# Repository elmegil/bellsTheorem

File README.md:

# bellsTheorem
[]

Bell's theorem is a proof that quantum physics is incompatible with local hidden variable theories.  The summary on Wikipedia is quite good if you’re interested in the quantum physics aspects of the theorem.

The proof is sometimes demonstrated by the use of multiple polarized lenses, as in this video:

https://www.youtube.com/watch?v=zcqZHYo7ONs&t=337s

What’s interesting is that with 3 or more polarized lenses, the behavior does not match what you might expect, namely that lens 1 reduces the light by a certain percentage, lens 2 reduces it further, and lens 3 reduces it even further, in a linear fashion.  If lens 3 and lens 1 are 90 degrees from each other, with nothing else involved, essentially no light gets through.  But if you insert lens 2 at a 45 degree angle to both of the others, suddenly there IS light getting through.  You’d expect that if 3 after 1 always blocks all the light, that would be true no matter what you put between the two.

A highly simplified explanation of this has to do with the fact that light is made up of photons, which are quantum objects.  Quantum objects behave probabilistically but ultimately are either there or not.  Photons going from lens 1 to lens 3 aren’t reduced in energy, they simply don’t pass both lenses.  However, going from one lens to one at 45 degrees only reduces the probability of photos passing by 50%.  In the process of going through, those photons then match the orientation of the second lens.  So when they get to a third lens, there is only a 45 degree angle difference there as well, and so 50% of the original 50%, or 25% of the original light, still passes through.

The rules for photons passing through polarized lenses basically are a probability that is determined entirely by the two lenses directly adjacent to the path of travel.  Any previous or subsequent lenses  aren’t considered except as a chained operation.  So with lens 1 at 0 degrees, lens 2 at 45, and lens 3 at 90 degrees (or 45 degrees from lens 2), the overall probability of a photon going from the start to the finish is 50% x 50%, or 25%.

Making things slightly weirder, the probabilities aren’t linear.  They follow a cosine squared relationship.  A photon passing through a pair of lenses at 22.5 degrees from each other is considerably more likely to pass through than the linear expectation of 75%.  In fact it’s about 85%.

============================================================================

Nyles Miszczyk on Facebook asked whether there were any modules that could process control voltages in this way.  There do not appear to be, but the idea was intriguing enough to give it a shot.  And that’s where this module comes from.

# Operational Notes

There is a single input voltage to be processed, which is normalled to +12V.  There are 4 encoders which represent the relative positions of four lenses, first to a “main” lens behind them all, and then relative to each other.  They’re arranged in a square pattern, and the input “light” (really the voltage) is processed as it goes through a single lens at 0 degrees, and then each subsequent lens.  Each of the combinations of lenses has a related output, so each of A, B, C, and D have an output that is only related to their individual angles relative to 0.  Each of AB, BC, CD, and DA has an output related to each of the intervening angles, as in the example described above; so for AB the voltage is reduced by whatever the probability is between 0 degrees and angle A, and then further reduced by whatever the probability is between the angles of A and B.  ABC, BCD, CDA, and DAB then follow the same rules for three lenses, and finally ABCD extends the process through all 4 lenses.

In addition to the encoders, each of the 4 lenses has a CV that is also related to its angle, added to the angle as set up by the encoder.  The 0 - 10V range maps to 180 degrees of rotation (positive only… need to consider doing otherwise).

On first power up, the lenses are reset to 0 degrees (but they should retain the last known state).  You can press each encoder to reset it to zero so that it’s at a known state.  If you do this by accident, pressing the encoder again takes you back to the saved state.  HOWEVER, if you zero out this way and then change things, you do do NOT save the new angle when you press again -- you just go back to the saved state, and pressing one more time takes you back to zero.

Voltage ranges: the current implementation limits inputs to 0-10V and each output will only generate 0-10V.  (and even that not very precisely).  A future revision may allow processing of bipolar input voltages, although this very likely will reduce the overall resolution.  Each input should be able to tolerate any normal Eurorack voltages outside this range (-12V to +12V), but they will be clamped at 0-10V.

Encoders:  the encoders’ positions are NOT directly mapped to the angle.  Most encoders only have about 24 steps (some have more, but none have 360 steps).  That did not seem to be a good resolution because each step would be 15 degrees.  I have mapped the encoders so that each step is 2 degrees of angle; this is why the press to reset is important so you can get back to a known angle. -- need to decide about CVs… 0 - 10V … is that 0 - 90 degrees?  0 - 180?  0 - 360?  Maybe consider 30 step encoders that do map the angle?  Is there any way to set up to display the angle, circle of LEDs on each encoder?  Is there sufficient space/bandwidth to update them?

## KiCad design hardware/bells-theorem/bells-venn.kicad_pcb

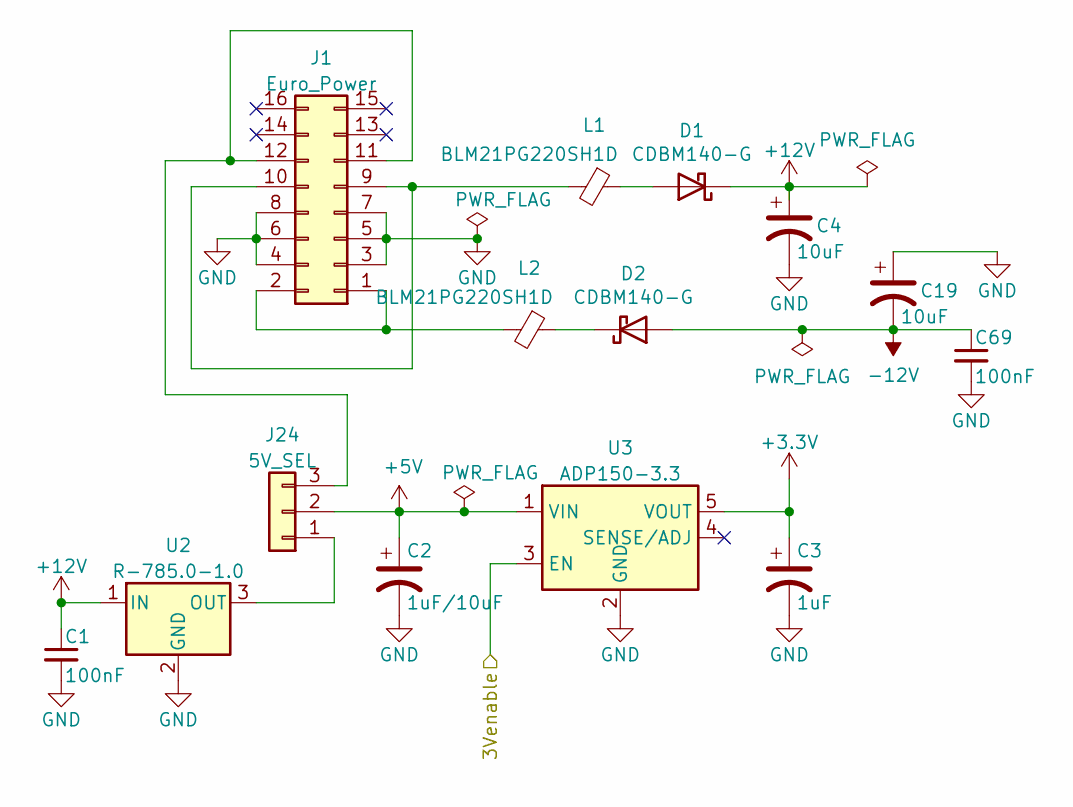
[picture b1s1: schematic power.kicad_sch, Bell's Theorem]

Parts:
C1, C69: 100nF; C_0805_2012Metric_Pad1.18x1.45mm_HandSolder
C2: 1uF/10uF; CP_Radial_D5.0mm_P2.50mm
C3: 1uF; CP_Radial_D5.0mm_P2.50mm
C4, C19: 10uF; CP_Radial_D5.0mm_P2.50mm
D1, D2: CDBM140-G; D_SMA-SMB_Universal_Handsoldering
J1: Euro_Power; IDC-Header_2x08_P2.54mm_Vertical
J24: 5V_SEL; PinHeader_1x03_P2.54mm_Vertical
L1, L2: BLM21PG220SH1D; L_0805_2012Metric_Pad1.15x1.40mm_HandSolder
U2: R-785.0-1.0; Converter_DCDC_RECOM_R-78E-0.5_THT
U3: ADP150-3.3; TSOT-23-5

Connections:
+3V3: C3.1, U3.5 (VOUT); also elsewhere on the board
+5V: C2.1, J24.2, U3.1 (VIN); also elsewhere on the board
+12V: C1.1, C4.1, D1.1 (K), U2.1 (IN); also elsewhere on the board
-12V: C19.2, C69.1, D2.2 (A); also elsewhere on the board
/main/3Venable: U3.3 (EN); also elsewhere on the board
GND: C1.2, C2.2, C3.2, C4.2, C19.1, C69.2, J1.3, J1.4, J1.5, J1.6, J1.7, J1.8, U2.2 (GND), U3.2 (GND); also elsewhere on the board
unnamed: D1.2 (A), L1.1
unnamed: D2.1 (K), L2.1
unnamed: J1.1, J1.2, L2.2
unnamed: J1.9, J1.10, L1.2
unnamed: J1.11, J1.12, J24.3
unnamed: J24.1, U2.3 (OUT)

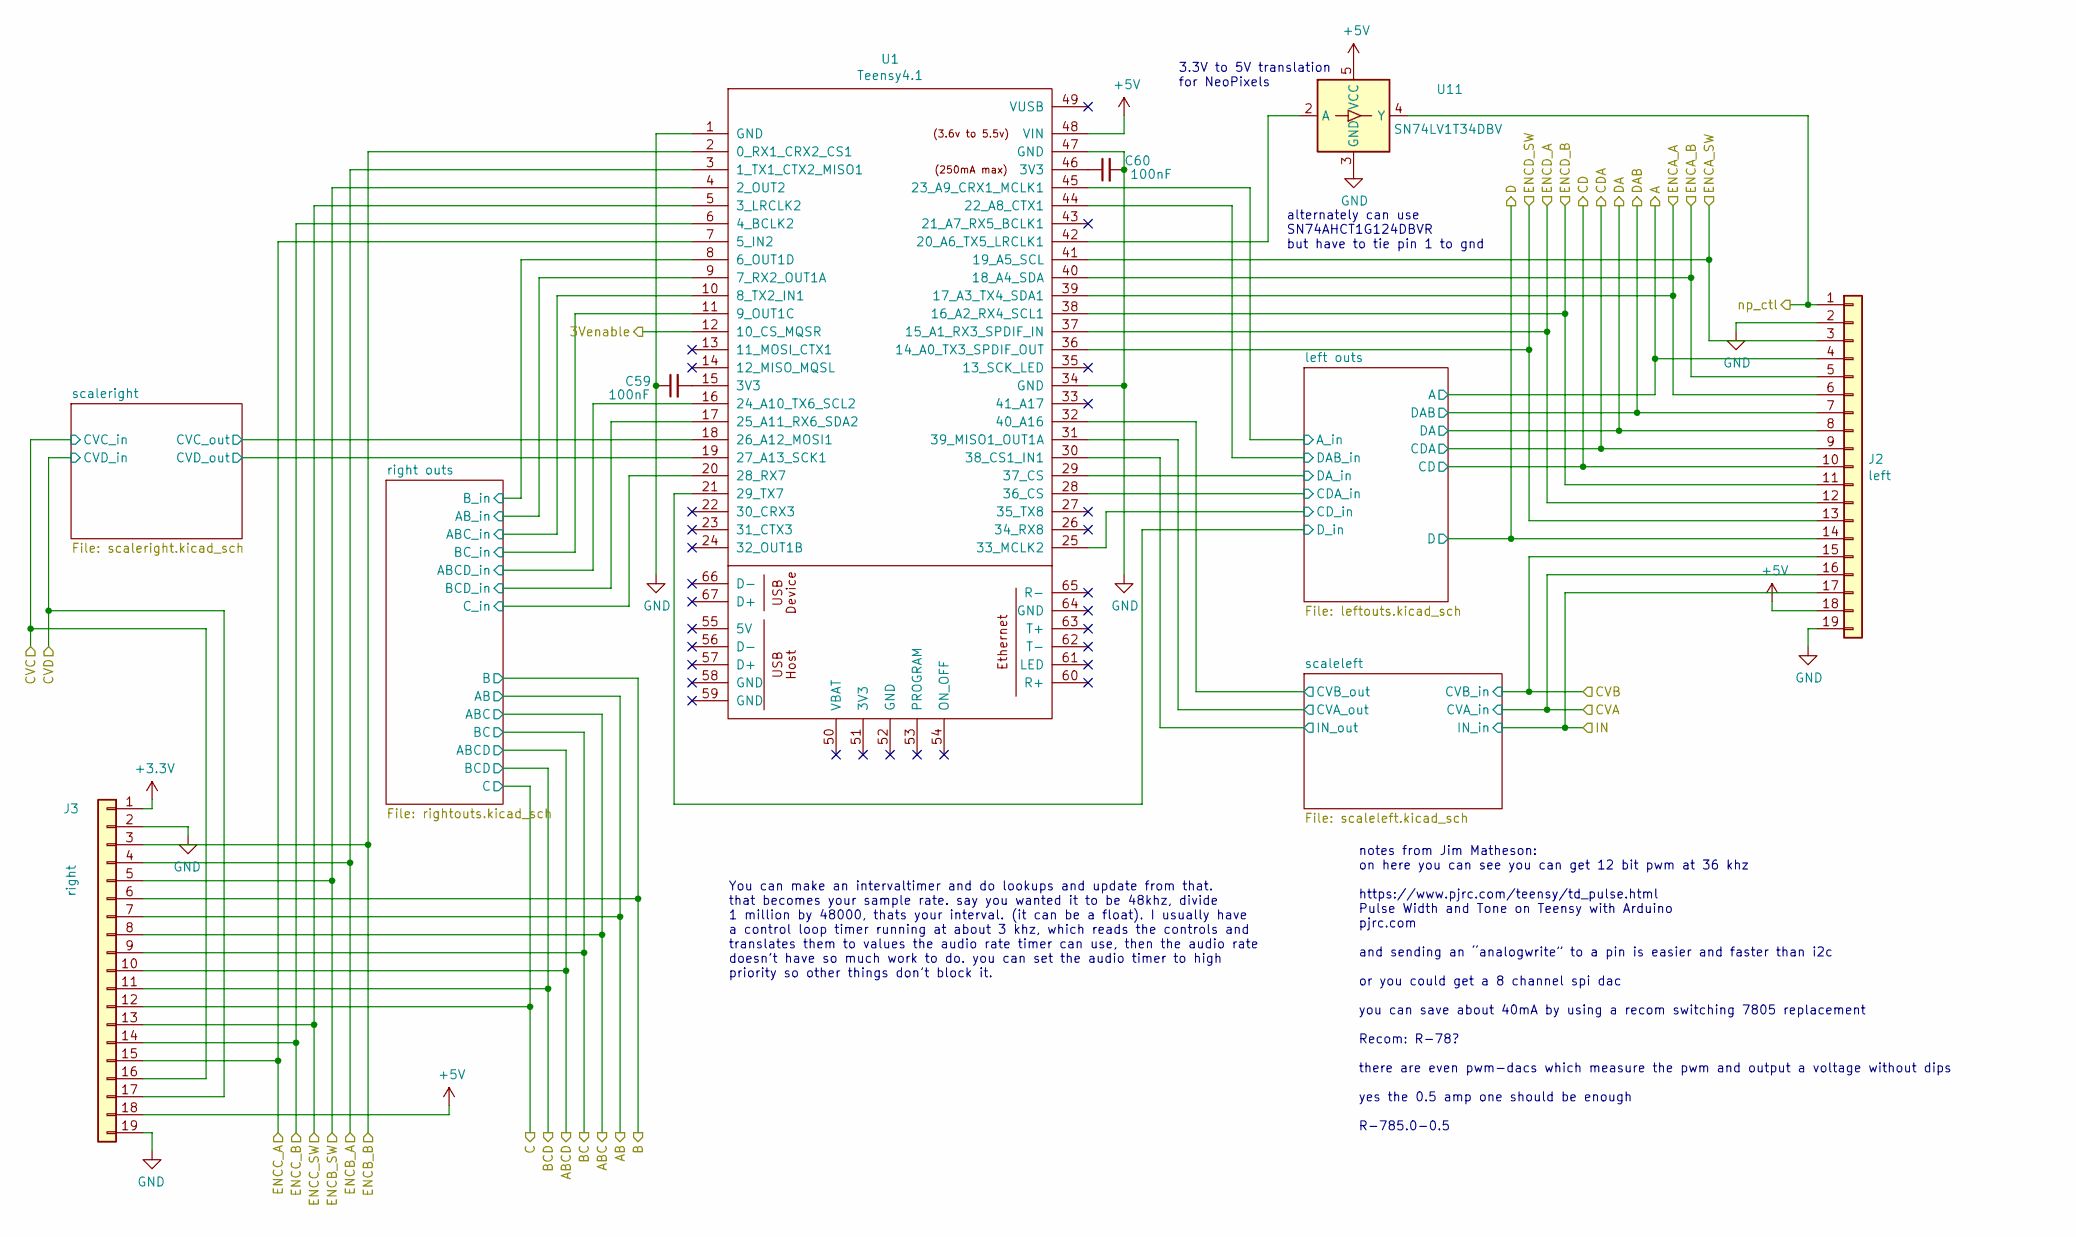
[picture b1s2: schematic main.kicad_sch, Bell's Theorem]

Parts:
C59, C60: 100nF; C_0805_2012Metric_Pad1.18x1.45mm_HandSolder
J2: left; PinSocket_1x19_P2.54mm_Vertical
J3: right; PinSocket_1x19_P2.54mm_Vertical
U1: Teensy4.1; Teensy41
U11: SN74LV1T34DBV; SOT-23-5

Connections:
+3V3: J3.1; also elsewhere on the board
+5V: J2.18, J3.18, U1.48 (VIN), U11.5 (VCC); also elsewhere on the board
/main/3Venable: U1.12 (10_CS_MQSR); also elsewhere on the board
/main/A: J2.4; also elsewhere on the board
/main/AB: J3.7; also elsewhere on the board
/main/ABC: J3.8; also elsewhere on the board
/main/ABCD: J3.10; also elsewhere on the board
/main/B: J3.6; also elsewhere on the board
/main/BC: J3.9; also elsewhere on the board
/main/BCD: J3.11; also elsewhere on the board
/main/C: J3.12; also elsewhere on the board
/main/CD: J2.10; also elsewhere on the board
/main/CDA: J2.9; also elsewhere on the board
/main/CVA: J2.16; also elsewhere on the board
/main/CVB: J2.15; also elsewhere on the board
/main/CVC: J3.16; also elsewhere on the board
/main/CVD: J3.17; also elsewhere on the board
/main/D: J2.14; also elsewhere on the board
/main/DA: J2.8; also elsewhere on the board
/main/DAB: J2.7; also elsewhere on the board
/main/ENCA_A: J2.6, U1.39 (17_A3_TX4_SDA1); also elsewhere on the board
/main/ENCA_B: J2.5, U1.40 (18_A4_SDA); also elsewhere on the board
/main/ENCA_SW: J2.3, U1.41 (19_A5_SCL); also elsewhere on the board
/main/ENCB_A: J3.4, U1.3 (1_TX1_CTX2_MISO1); also elsewhere on the board
/main/ENCB_B: J3.3, U1.2 (0_RX1_CRX2_CS1); also elsewhere on the board
/main/ENCB_SW: J3.5, U1.4 (2_OUT2); also elsewhere on the board
/main/ENCC_A: J3.15, U1.7 (5_IN2); also elsewhere on the board
/main/ENCC_B: J3.14, U1.6 (4_BCLK2); also elsewhere on the board
/main/ENCC_SW: J3.13, U1.5 (3_LRCLK2); also elsewhere on the board
/main/ENCD_A: J2.12, U1.37 (15_A1_RX3_SPDIF_IN); also elsewhere on the board
/main/ENCD_B: J2.11, U1.38 (16_A2_RX4_SCL1); also elsewhere on the board
/main/ENCD_SW: J2.13, U1.36 (14_A0_TX3_SPDIF_OUT); also elsewhere on the board
/main/IN: J2.17; also elsewhere on the board
/main/left outs/A_in: U1.45 (23_A9_CRX1_MCLK1); also elsewhere on the board
/main/left outs/CDA_in: U1.28 (36_CS); also elsewhere on the board
/main/left outs/CD_in: U1.25 (33_MCLK2); also elsewhere on the board
/main/left outs/DAB_in: U1.44 (22_A8_CTX1); also elsewhere on the board
/main/left outs/DA_in: U1.29 (37_CS); also elsewhere on the board
/main/left outs/D_in: U1.21 (29_TX7); also elsewhere on the board
/main/np_ctl: J2.1, U11.4 (Y); also elsewhere on the board
/main/right outs/ABCD_in: U1.16 (24_A10_TX6_SCL2); also elsewhere on the board
/main/right outs/ABC_in: U1.10 (8_TX2_IN1); also elsewhere on the board
/main/right outs/AB_in: U1.9 (7_RX2_OUT1A); also elsewhere on the board
/main/right outs/BCD_in: U1.17 (25_A11_RX6_SDA2); also elsewhere on the board
/main/right outs/BC_in: U1.11 (9_OUT1C); also elsewhere on the board
/main/right outs/B_in: U1.8 (6_OUT1D); also elsewhere on the board
/main/right outs/C_in: U1.20 (28_RX7); also elsewhere on the board
/main/scaleleft/CVA_out: U1.31 (39_MISO1_OUT1A); also elsewhere on the board
/main/scaleleft/CVB_out: U1.32 (40_A16); also elsewhere on the board
/main/scaleleft/IN_out: U1.30 (38_CS1_IN1); also elsewhere on the board
/main/scaleright/CVC_out: U1.18 (26_A12_MOSI1); also elsewhere on the board
/main/scaleright/CVD_out: U1.19 (27_A13_SCK1); also elsewhere on the board
GND: C59.1, C60.2, J2.2, J2.19, J3.2, J3.19, U1.1 (GND), U1.34 (GND), U1.47 (GND), U11.3 (GND); also elsewhere on the board
unnamed: C59.2, U1.15 (3V3)
unnamed: C60.1, U1.46 (3V3)
unnamed: U1.42 (20_A6_TX5_LRCLK1), U11.2 (A)

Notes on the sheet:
You can make an intervaltimer and do lookups and update from that. that becomes your sample rate. say you wanted it to be 48khz, divide 1 million by 48000, thats your interval. (it can be a float). I usually have a control loop timer running at about 3 khz, which reads the controls and translates t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
notes from Jim Matheson: on here you can see you can get 12 bit pwm at 36 khz https://www.pjrc.com/teensy/td_pulse.html Pulse Width and Tone on Teensy with Arduino pjrc.com and sending an “analogwrite” to a pin is easier and faster than i2c or you could get a 8 channel spi dac you can save about 40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
3.3V to 5V translation for NeoPixels
alternately can use SN74AHCT1G124DBVR but have to tie pin 1 to gnd

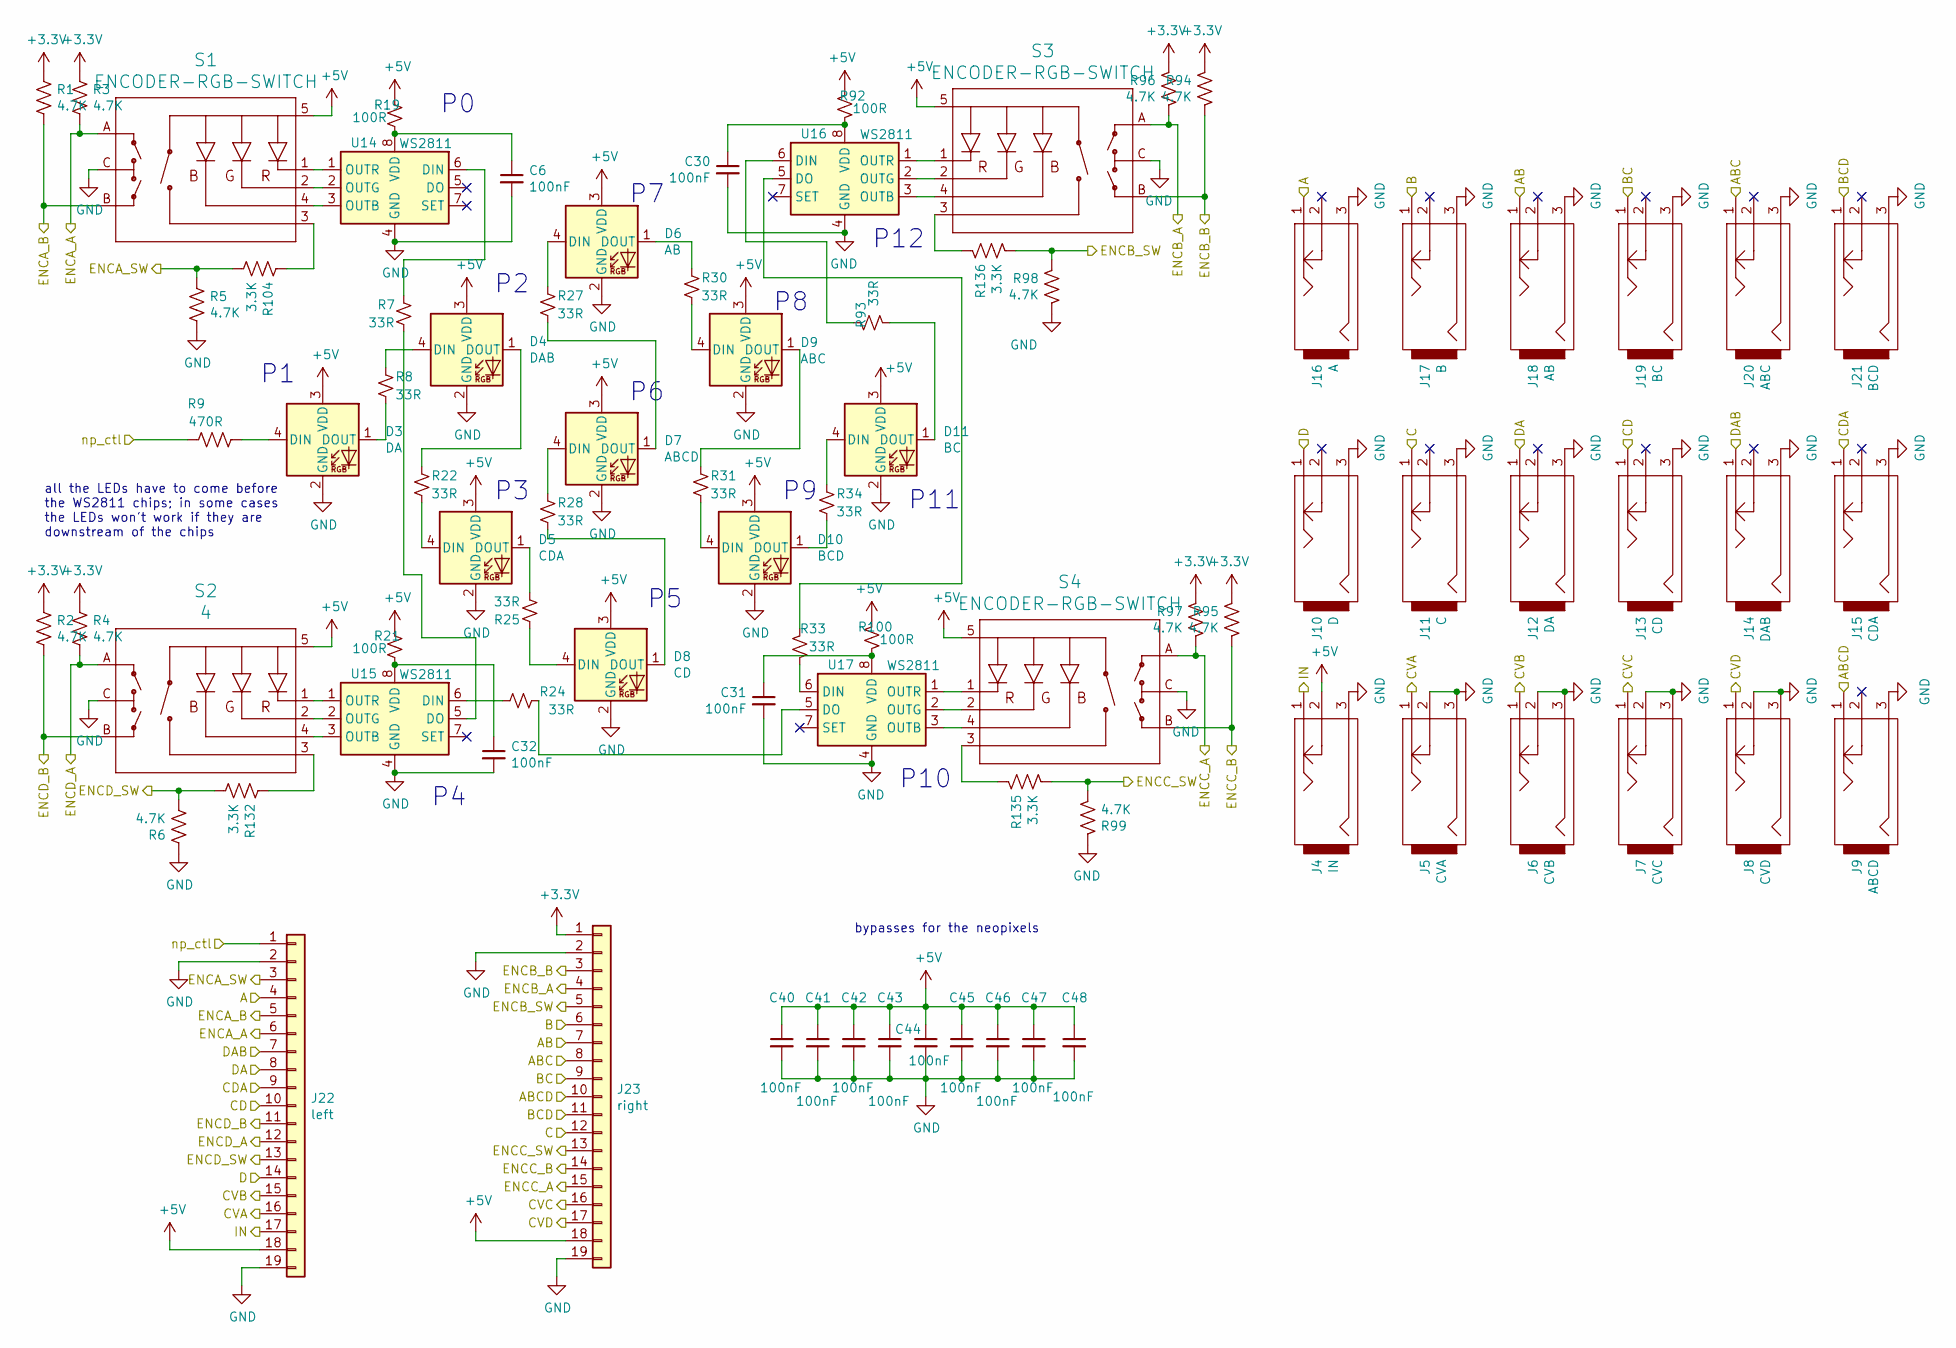
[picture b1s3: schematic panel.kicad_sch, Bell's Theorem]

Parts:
C6, C30, C31, C32, C40, C41, C42, C43, C44, C45, C46, C47, C48: 100nF; C_0805_2012Metric_Pad1.18x1.45mm_HandSolder
D3: DA; LED_D5.0mm-4_RGB
D4: DAB; LED_D5.0mm-4_RGB
D5: CDA; LED_D5.0mm-4_RGB
D6: AB; LED_D5.0mm-4_RGB
D7: ABCD; LED_D5.0mm-4_RGB
D8: CD; LED_D5.0mm-4_RGB
D9: ABC; LED_D5.0mm-4_RGB
D10: BCD; LED_D5.0mm-4_RGB
D11: BC; LED_D5.0mm-4_RGB
J4: IN; thonkiconn
J5: CVA; thonkiconn
J6: CVB; thonkiconn
J7: CVC; thonkiconn
J8: CVD; thonkiconn
J9: ABCD; thonkiconn
J10: D; thonkiconn
J11: C; thonkiconn
J12: DA; thonkiconn
J13: CD; thonkiconn
J14: DAB; thonkiconn
J15: CDA; thonkiconn
J16: A; thonkiconn
J17: B; thonkiconn
J18: AB; thonkiconn
J19: BC; thonkiconn
J20: ABC; thonkiconn
J21: BCD; thonkiconn
J22: left; PinHeader_1x19_P2.54mm_Vertical
J23: right; PinHeader_1x19_P2.54mm_Vertical
R1, R2, R3, R4, R5, R6, R94, R95, R96, R97, R98, R99: 4.7K; R_0805_2012Metric_Pad1.20x1.40mm_HandSolder
R7, R8, R22, R24, R25, R27, R28, R30, R31, R33, R34, R93: 33R; R_0805_2012Metric_Pad1.20x1.40mm_HandSolder
R9: 470R; R_0805_2012Metric_Pad1.20x1.40mm_HandSolder
R19, R21, R92, R100: 100R; R_0805_2012Metric_Pad1.20x1.40mm_HandSolder
R104, R132, R135, R136: 3.3K; R_0805_2012Metric_Pad1.20x1.40mm_HandSolder
S1, S3, S4: ENCODER-RGB-SWITCH; ENCODER_LED_3_KIT
S2: 4; ENCODER_LED_3_KIT
U14, U15, U16, U17: WS2811; SOIC-8_3.9x4.9mm_P1.27mm

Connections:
+3V3: J23.1, R1.1, R2.1, R3.1, R4.1, R94.1, R95.1, R96.1, R97.1; also elsewhere on the board
+5V: C40.1, C41.1, C42.1, C43.1, C44.1, C45.1, C46.1, C47.1, C48.1, D3.3 (VDD), D4.3 (VDD), D5.3 (VDD), D6.3 (VDD), D7.3 (VDD), D8.3 (VDD), D9.3 (VDD), D10.3 (VDD), D11.3 (VDD), J4.2, J22.18, J23.18, R19.1, R21.1, R92.1, R100.1, S1.5 (+), S2.5 (+), S3.5 (+), S4.5 (+); also elsewhere on the board
/main/A: J16.1, J22.4; also elsewhere on the board
/main/AB: J18.1, J23.7; also elsewhere on the board
/main/ABC: J20.1, J23.8; also elsewhere on the board
/main/ABCD: J9.1, J23.10; also elsewhere on the board
/main/B: J17.1, J23.6; also elsewhere on the board
/main/BC: J19.1, J23.9; also elsewhere on the board
/main/BCD: J21.1, J23.11; also elsewhere on the board
/main/C: J11.1, J23.12; also elsewhere on the board
/main/CD: J13.1, J22.10; also elsewhere on the board
/main/CDA: J15.1, J22.9; also elsewhere on the board
/main/CVA: J5.1, J22.16; also elsewhere on the board
/main/CVB: J6.1, J22.15; also elsewhere on the board
/main/CVC: J7.1, J23.16; also elsewhere on the board
/main/CVD: J8.1, J23.17; also elsewhere on the board
/main/D: J10.1, J22.14; also elsewhere on the board
/main/DA: J12.1, J22.8; also elsewhere on the board
/main/DAB: J14.1, J22.7; also elsewhere on the board
/main/ENCA_A: J22.6, R3.2, S1.A; also elsewhere on the board
/main/ENCA_B: J22.5, R1.2, S1.B; also elsewhere on the board
/main/ENCA_SW: J22.3, R5.1, R104.2; also elsewhere on the board
/main/ENCB_A: J23.4, R96.2, S3.A; also elsewhere on the board
/main/ENCB_B: J23.3, R94.2, S3.B; also elsewhere on the board
/main/ENCB_SW: J23.5, R98.1, R136.2; also elsewhere on the board
/main/ENCC_A: J23.15, R97.2, S4.A; also elsewhere on the board
/main/ENCC_B: J23.14, R95.2, S4.B; also elsewhere on the board
/main/ENCC_SW: J23.13, R99.2, R135.2; also elsewhere on the board
/main/ENCD_A: J22.12, R4.2, S2.A; also elsewhere on the board
/main/ENCD_B: J22.11, R2.2, S2.B; also elsewhere on the board
/main/ENCD_SW: J22.13, R6.2, R132.2; also elsewhere on the board
/main/IN: J4.1, J22.17; also elsewhere on the board
/main/np_ctl: J22.1, R9.1; also elsewhere on the board
GND: C6.2, C30.2, C31.2, C32.2, C40.2, C41.2, C42.2, C43.2, C44.2, C45.2, C46.2, C47.2, C48.2, D3.2 (GND), D4.2 (GND), D5.2 (GND), D6.2 (GND), D7.2 (GND), D8.2 (GND), D9.2 (GND), D10.2 (GND), D11.2 (GND), J4.3, J5.2, J5.3, J6.2, J6.3, J7.2, J7.3, J8.2, J8.3, J9.3, J10.3, J11.3, J12.3, J13.3, J14.3, J15.3, J16.3, J17.3, J18.3, J19.3, J20.3, J21.3, J22.2, J22.19, J23.2, J23.19, R5.2, R6.1, R98.2, R99.1, S1.C, S2.C, S3.C, S4.C, U14.4 (GND), U15.4 (GND), U16.4 (GND), U17.4 (GND); also elsewhere on the board
unnamed: C6.1, R19.2, U14.8 (VDD)
unnamed: C30.1, R92.2, U16.8 (VDD)
unnamed: C31.1, R100.2, U17.8 (VDD)
unnamed: C32.1, R21.2, U15.8 (VDD)
unnamed: D3.1 (DOUT), R8.2
unnamed: D3.4 (DIN), R9.2
unnamed: D4.1 (DOUT), R22.1
unnamed: D4.4 (DIN), R8.1
unnamed: D5.1 (DOUT), R25.2
unnamed: D5.4 (DIN), R22.2
unnamed: D6.1 (DOUT), R30.1
unnamed: D6.4 (DIN), R27.1
unnamed: D7.1 (DOUT), R27.2
unnamed: D7.4 (DIN), R28.1
unnamed: D8.1 (DOUT), R28.2
unnamed: D8.4 (DIN), R25.1
unnamed: D9.1 (DOUT), R31.1
unnamed: D9.4 (DIN), R30.2
unnamed: D10.1 (DOUT), R34.2
unnamed: D10.4 (DIN), R31.2
unnamed: D11.1 (DOUT), R93.2
unnamed: D11.4 (DIN), R34.1
unnamed: R7.1, U14.6 (DIN)
unnamed: R7.2, U15.5 (DO)
unnamed: R24.1, U17.5 (DO)
unnamed: R24.2, U15.6 (DIN)
unnamed: R33.1, U16.5 (DO)
unnamed: R33.2, U17.6 (DIN)
unnamed: R93.1, U16.6 (DIN)
unnamed: R104.1, S1.3 (SW)
unnamed: R132.1, S2.3 (SW)
unnamed: R135.1, S4.3 (SW)
unnamed: R136.1, S3.3 (SW)
unnamed: S1.1 (-R), U14.1 (OUTR)
unnamed: S1.2 (-G), U14.2 (OUTG)
unnamed: S1.4 (-B), U14.3 (OUTB)
unnamed: S2.1 (-R), U15.1 (OUTR)
unnamed: S2.2 (-G), U15.2 (OUTG)
unnamed: S2.4 (-B), U15.3 (OUTB)
unnamed: S3.1 (-R), U16.1 (OUTR)
unnamed: S3.2 (-G), U16.2 (OUTG)
unnamed: S3.4 (-B), U16.3 (OUTB)
unnamed: S4.1 (-R), U17.1 (OUTR)
unnamed: S4.2 (-G), U17.2 (OUTG)
unnamed: S4.4 (-B), U17.3 (OUTB)

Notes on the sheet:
bypasses for the neopixels
all the LEDs have to come before the WS2811 chips; in some cases the LEDs won't work if they are downstream of the chips
P12
P11
P10

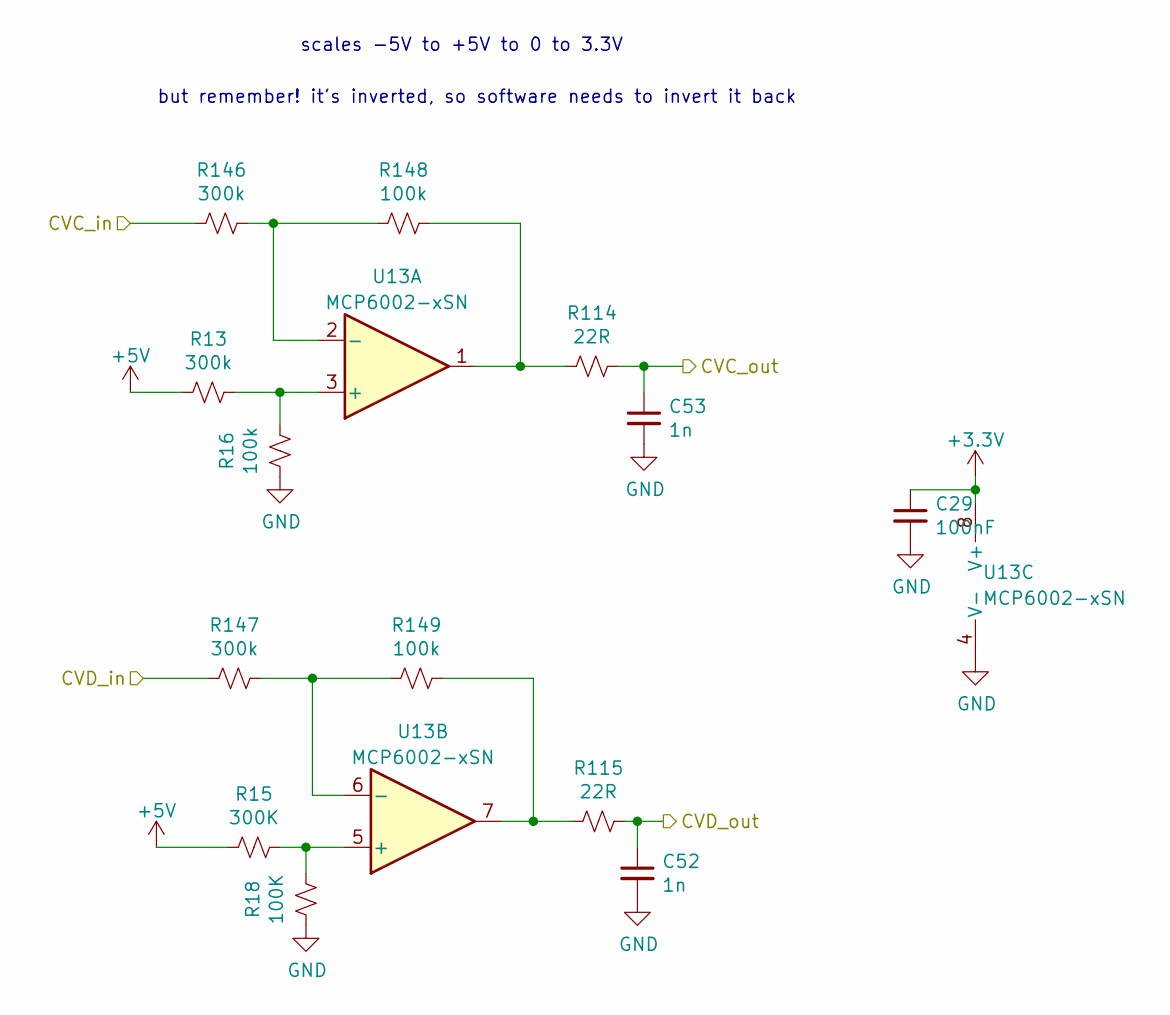
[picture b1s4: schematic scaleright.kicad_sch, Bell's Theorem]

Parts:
C29: 100nF; C_0805_2012Metric_Pad1.18x1.45mm_HandSolder
C52, C53: 1n; C_0805_2012Metric_Pad1.18x1.45mm_HandSolder
R13, R146, R147: 300k; R_0805_2012Metric_Pad1.20x1.40mm_HandSolder
R15: 300K; R_0805_2012Metric_Pad1.20x1.40mm_HandSolder
R16, R148, R149: 100k; R_0805_2012Metric_Pad1.20x1.40mm_HandSolder
R18: 100K; R_0805_2012Metric_Pad1.20x1.40mm_HandSolder
R114, R115: 22R; R_0805_2012Metric_Pad1.20x1.40mm_HandSolder
U13: MCP6002-xSN; SOIC-8_3.9x4.9mm_P1.27mm

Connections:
+3V3: C29.1, U13.8 (V+); also elsewhere on the board
+5V: R13.2, R15.2; also elsewhere on the board
/main/CVC: R146.2; also elsewhere on the board
/main/CVD: R147.2; also elsewhere on the board
/main/scaleright/CVC_out: C53.1, R114.1; also elsewhere on the board
/main/scaleright/CVD_out: C52.1, R115.1; also elsewhere on the board
GND: C29.2, C52.2, C53.2, R16.2, R18.2, U13.4 (V-); also elsewhere on the board
unnamed: R13.1, R16.1, U13.3 (+)
unnamed: R15.1, R18.1, U13.5 (+)
unnamed: R114.2, R148.1, U13.1
unnamed: R115.2, R149.1, U13.7
unnamed: R146.1, R148.2, U13.2 (-)
unnamed: R147.1, R149.2, U13.6 (-)

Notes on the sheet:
but remember! it's inverted, so software needs to invert it back
scales -5V to +5V to 0 to 3.3V

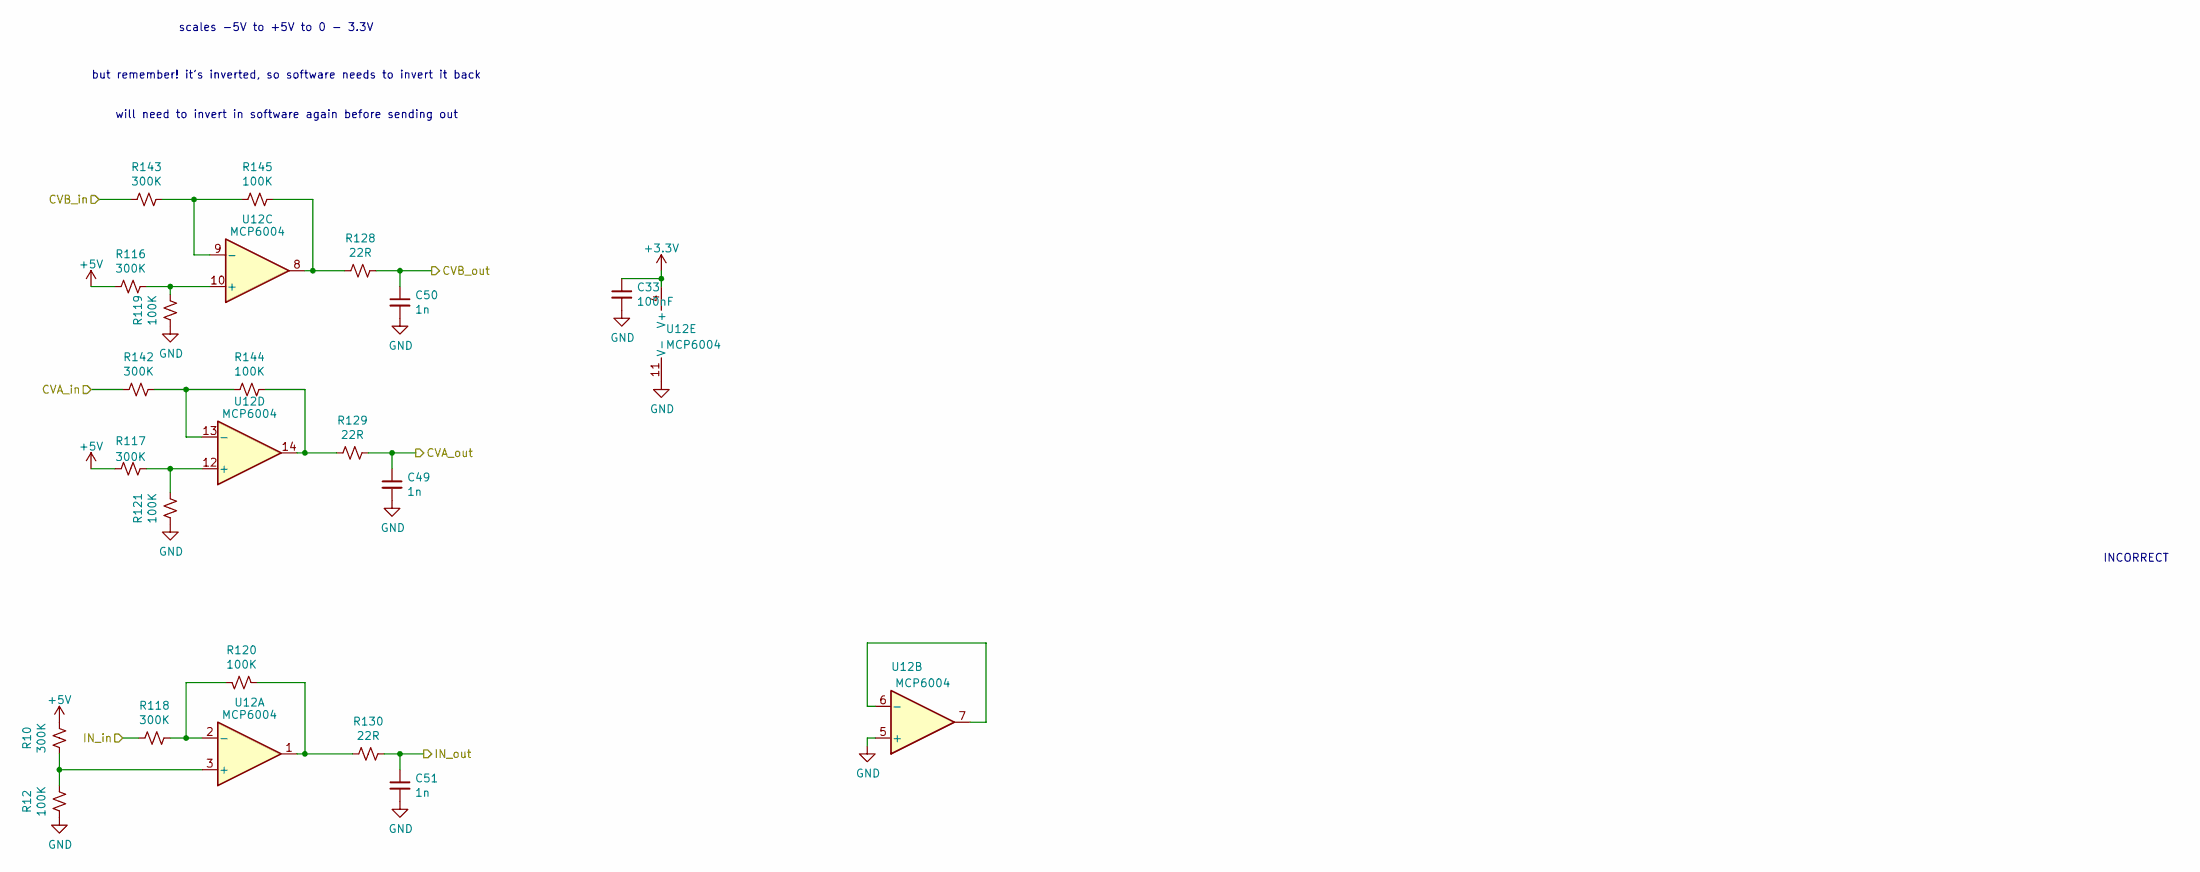
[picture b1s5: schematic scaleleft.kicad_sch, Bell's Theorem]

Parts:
C33: 100nF; C_0805_2012Metric_Pad1.18x1.45mm_HandSolder
C49, C50, C51: 1n; C_0805_2012Metric_Pad1.18x1.45mm_HandSolder
R10, R116, R117, R118, R142, R143: 300K; R_0805_2012Metric_Pad1.20x1.40mm_HandSolder
R12, R119, R120, R121, R144, R145: 100K; R_0805_2012Metric_Pad1.20x1.40mm_HandSolder
R128, R129, R130: 22R; R_0805_2012Metric_Pad1.20x1.40mm_HandSolder
U12: MCP6004; SO-14_3.9x8.65mm_P1.27mm

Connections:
+3V3: C33.1, U12.4 (V+); also elsewhere on the board
+5V: R10.1, R116.2, R117.2; also elsewhere on the board
/main/CVA: R142.2; also elsewhere on the board
/main/CVB: R143.2; also elsewhere on the board
/main/IN: R118.2; also elsewhere on the board
/main/scaleleft/CVA_out: C49.1, R129.1; also elsewhere on the board
/main/scaleleft/CVB_out: C50.1, R128.1; also elsewhere on the board
/main/scaleleft/IN_out: C51.1, R130.1; also elsewhere on the board
GND: C33.2, C49.2, C50.2, C51.2, R12.2, R119.2, R121.2, U12.5 (+), U12.11 (V-); also elsewhere on the board
unnamed: R10.2, R12.1, U12.3 (+)
unnamed: R116.1, R119.1, U12.10 (+)
unnamed: R117.1, R121.1, U12.12 (+)
unnamed: R118.1, R120.1, U12.2 (-)
unnamed: R120.2, R130.2, U12.1
unnamed: R128.2, R145.1, U12.8
unnamed: R129.2, R144.1, U12.14
unnamed: R142.1, R144.2, U12.13 (-)
unnamed: R143.1, R145.2, U12.9 (-)
unnamed: U12.6 (-), U12.7

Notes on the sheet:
INCORRECT
will need to invert in software again before sending out
scales -5V to +5V to 0 - 3.3V
but remember! it's inverted, so software needs to invert it back

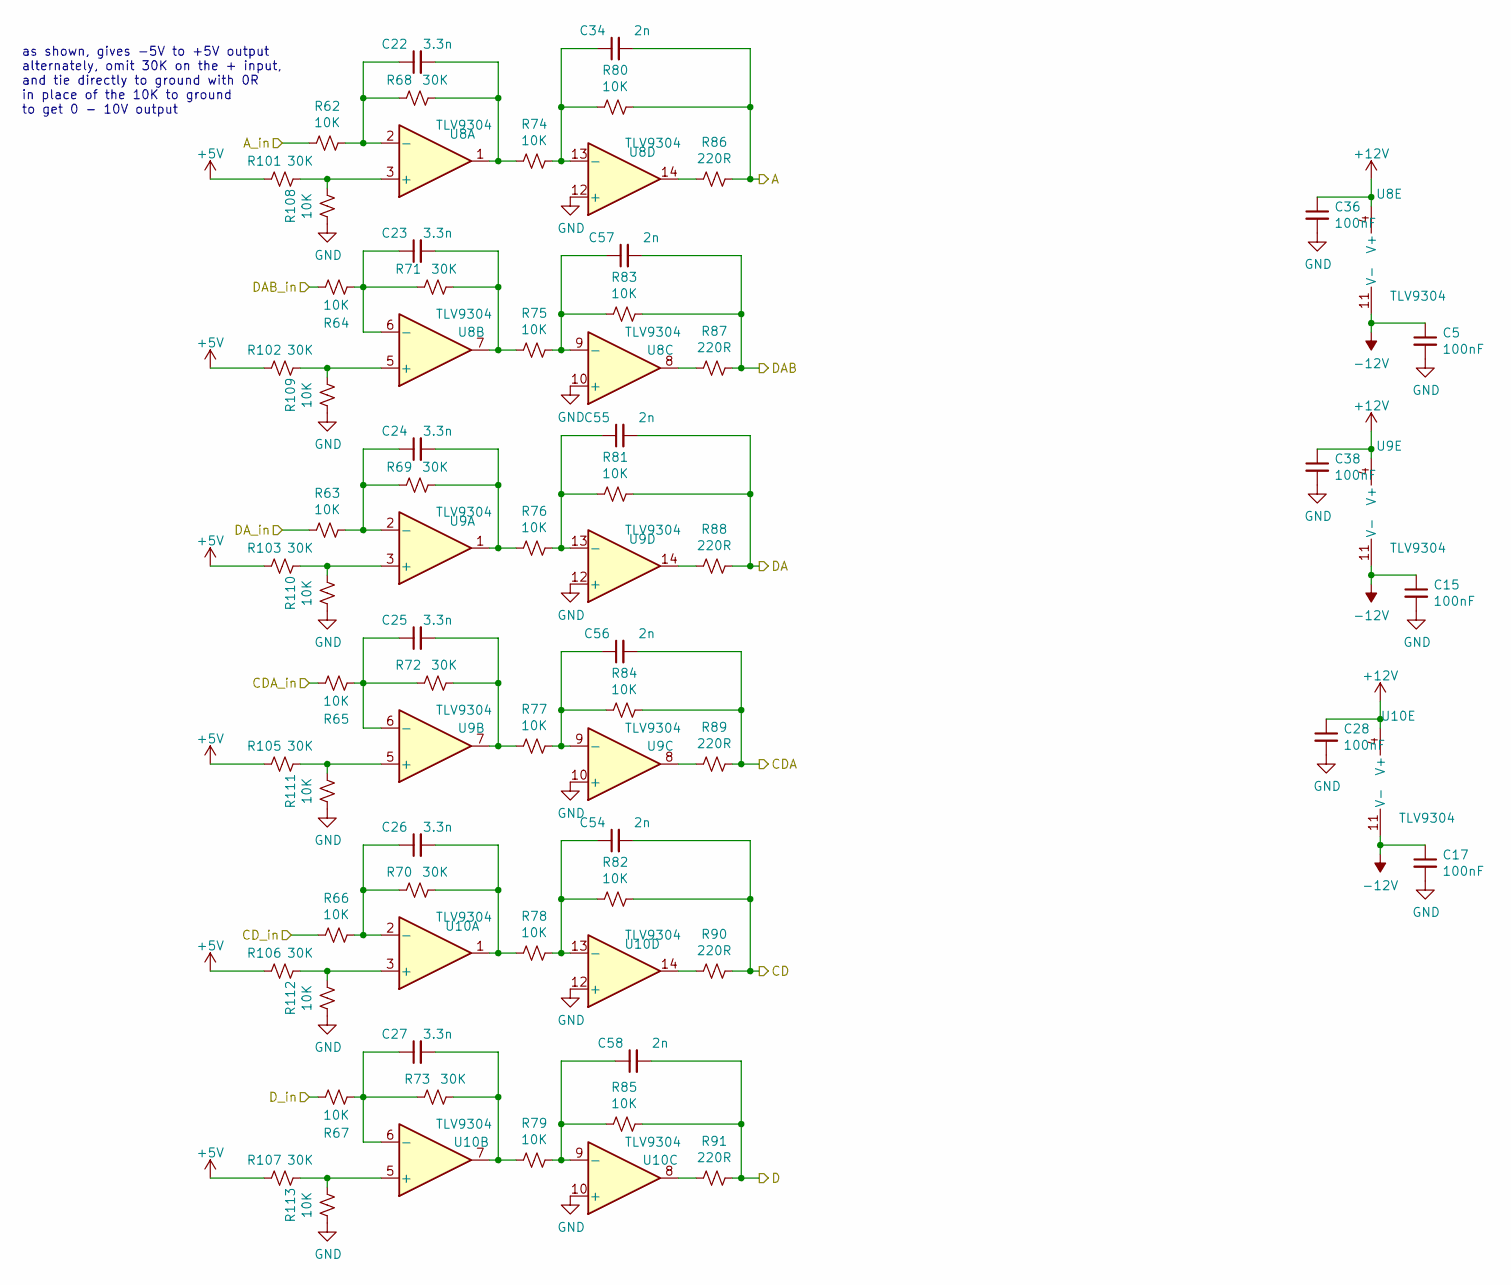
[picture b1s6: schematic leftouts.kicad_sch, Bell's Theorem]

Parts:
C5, C15, C17, C28, C36, C38: 100nF; C_0805_2012Metric_Pad1.18x1.45mm_HandSolder
C22, C23, C24, C25, C26, C27: 3.3n; C_0805_2012Metric_Pad1.18x1.45mm_HandSolder
C34, C54, C55, C56, C57, C58: 2n; C_0805_2012Metric_Pad1.18x1.45mm_HandSolder
R62, R63, R64, R65, R66, R67, R74, R75, R76, R77, R78, R79, R80, R81, R82, R83, R84, R85, R108, R109, R110, R111, R112, R113: 10K; R_0805_2012Metric_Pad1.20x1.40mm_HandSolder
R68, R69, R70, R71, R72, R73, R101, R102, R103, R105, R106, R107: 30K; R_0805_2012Metric_Pad1.20x1.40mm_HandSolder
R86, R87, R88, R89, R90, R91: 220R; R_0805_2012Metric_Pad1.20x1.40mm_HandSolder
U8, U9, U10: TLV9304; SOIC-14_3.9x8.7mm_P1.27mm

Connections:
+5V: R101.2, R102.2, R103.2, R105.2, R106.2, R107.2; also elsewhere on the board
+12V: C28.1, C36.1, C38.1, U8.4 (V+), U9.4 (V+), U10.4 (V+); also elsewhere on the board
-12V: C5.1, C15.1, C17.1, U8.11 (V-), U9.11 (V-), U10.11 (V-); also elsewhere on the board
/main/A: C34.2, R80.1, R86.1; also elsewhere on the board
/main/CD: C54.2, R82.1, R90.1; also elsewhere on the board
/main/CDA: C56.2, R84.1, R89.1; also elsewhere on the board
/main/D: C58.2, R85.1, R91.1; also elsewhere on the board
/main/DA: C55.2, R81.1, R88.1; also elsewhere on the board
/main/DAB: C57.2, R83.1, R87.1; also elsewhere on the board
/main/left outs/A_in: R62.2; also elsewhere on the board
/main/left outs/CDA_in: R65.2; also elsewhere on the board
/main/left outs/CD_in: R66.2; also elsewhere on the board
/main/left outs/DAB_in: R64.2; also elsewhere on the board
/main/left outs/DA_in: R63.2; also elsewhere on the board
/main/left outs/D_in: R67.2; also elsewhere on the board
GND: C5.2, C15.2, C17.2, C28.2, C36.2, C38.2, R108.2, R109.2, R110.2, R111.2, R112.2, R113.2, U8.10 (+), U8.12 (+), U9.10 (+), U9.12 (+), U10.10 (+), U10.12 (+); also elsewhere on the board
unnamed: C22.1, R62.1, R68.2, U8.2 (-)
unnamed: C22.2, R68.1, R74.2, U8.1
unnamed: C23.1, R64.1, R71.2, U8.6 (-)
unnamed: C23.2, R71.1, R75.2, U8.7
unnamed: C24.1, R63.1, R69.2, U9.2 (-)
unnamed: C24.2, R69.1, R76.2, U9.1
unnamed: C25.1, R65.1, R72.2, U9.6 (-)
unnamed: C25.2, R72.1, R77.2, U9.7
unnamed: C26.1, R66.1, R70.2, U10.2 (-)
unnamed: C26.2, R70.1, R78.2, U10.1
unnamed: C27.1, R67.1, R73.2, U10.6 (-)
unnamed: C27.2, R73.1, R79.2, U10.7
unnamed: C34.1, R74.1, R80.2, U8.13 (-)
unnamed: C54.1, R78.1, R82.2, U10.13 (-)
unnamed: C55.1, R76.1, R81.2, U9.13 (-)
unnamed: C56.1, R77.1, R84.2, U9.9 (-)
unnamed: C57.1, R75.1, R83.2, U8.9 (-)
unnamed: C58.1, R79.1, R85.2, U10.9 (-)
unnamed: R86.2, U8.14
unnamed: R87.2, U8.8
unnamed: R88.2, U9.14
unnamed: R89.2, U9.8
unnamed: R90.2, U10.14
unnamed: R91.2, U10.8
unnamed: R101.1, R108.1, U8.3 (+)
unnamed: R102.1, R109.1, U8.5 (+)
unnamed: R103.1, R110.1, U9.3 (+)
unnamed: R105.1, R111.1, U9.5 (+)
unnamed: R106.1, R112.1, U10.3 (+)
unnamed: R107.1, R113.1, U10.5 (+)

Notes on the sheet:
as shown, gives -5V to +5V output alternately, omit 30K on the + input, and tie directly to ground with 0R in place of the 10K to ground to get 0 - 10V output

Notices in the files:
README.md:
License: CC BY-NC 4.0
hardware/bells-theorem/bells-venn.kicad_pcb:
Copyright (c) 2023
